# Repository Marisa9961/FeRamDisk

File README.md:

# FeRamDisk: 基于 STM32G431 的铁电存储 U 盘

## 项目概述
FeRamDisk 是一款基于 **STM32G431** 主控与 **MB85RS256** 存储介质的专用闪存盘。

不同于传统的 NAND Flash 存储方案，本项目利用铁电随机存取存储器（FeRAM）的物理特性，实现了极高的读写耐久性与近乎瞬时的随机访问能力。

硬件设计中使用了四片并列的 **MB85RS256** ，单片容量为 32 kB（即 256 Kbit），总计达到的存储空间为 128 kB。

## 功能介绍

1. **硬件设计开源**：提供完整的 Kicad 工程、原理图及制造文件，可直接打板生产。
2. **USB 大容量存储设备固件设计**：基于 Rust embassy 异步框架，从零实现 SCSI 指令集与 BOT 协议，支持全平台免驱识别。
3. **影子存储区防止文件系统崩溃**：利用日志机制抽象存储操作，保障意外断电及插拔时的数据一致性。

## 快速上手

项目固件采用 Rust 编写。构建前请确保已安装 Rust 工具链。

```bash
cd firmware

# 编译固件（默认已启用 hardware feature）
cargo build --release

# 在主机上运行脱离硬件的单元测试（需关闭默认的硬件功能并指定主机平台）
# 另外需要根据自己的开发环境选择正确的目标平台
cargo test --no-default-features --target x86_64-pc-windows-msvc

# 如果已配置 probe-rs 等烧录工具，可直接一键编译并烧录
cargo run --release
```

## 项目构成

- `hardware/`: 硬件设计目录（包含 Kicad 源工程、BOM 表及 Gerber 生产文件）。
- `firmware/`: 核心固件目录（Rust 编写）。
  - `src/usb/`: USB 核心协议栈（MSC / BOT / SCSI）的具体实现。
  - `src/storage/`: 存储后端适配与事务日志系统（Journaling），确保块设备的高可靠读写。
  - `src/drivers/`: SPI 通信底漆及 MB85RS256 铁电存储芯片的驱动层。
  - `tests/`: 包含脱离硬件直接在 PC 端运行的协议栈软仿真测试环境。
- `docs/`: 相关的项目说明与文档资源。

## 贡献要点

欢迎任何形式的讨论与代码贡献（Pull Request / Issue）：
1. **固件开发**：PR 提交前，请确保能够通过 `tests/` 目录下的所有软仿真单元测试 (`cargo test`)。
2. **硬件优化**：如有 PCB 布局或元器件替代方案，请提供原因及 Kicad 源文件的修改。
3. **想法拓展**：欢迎探讨铁电特性（极快且无磨损限制）在微型数据记录器（Data Logger）等前沿领域的新用法。

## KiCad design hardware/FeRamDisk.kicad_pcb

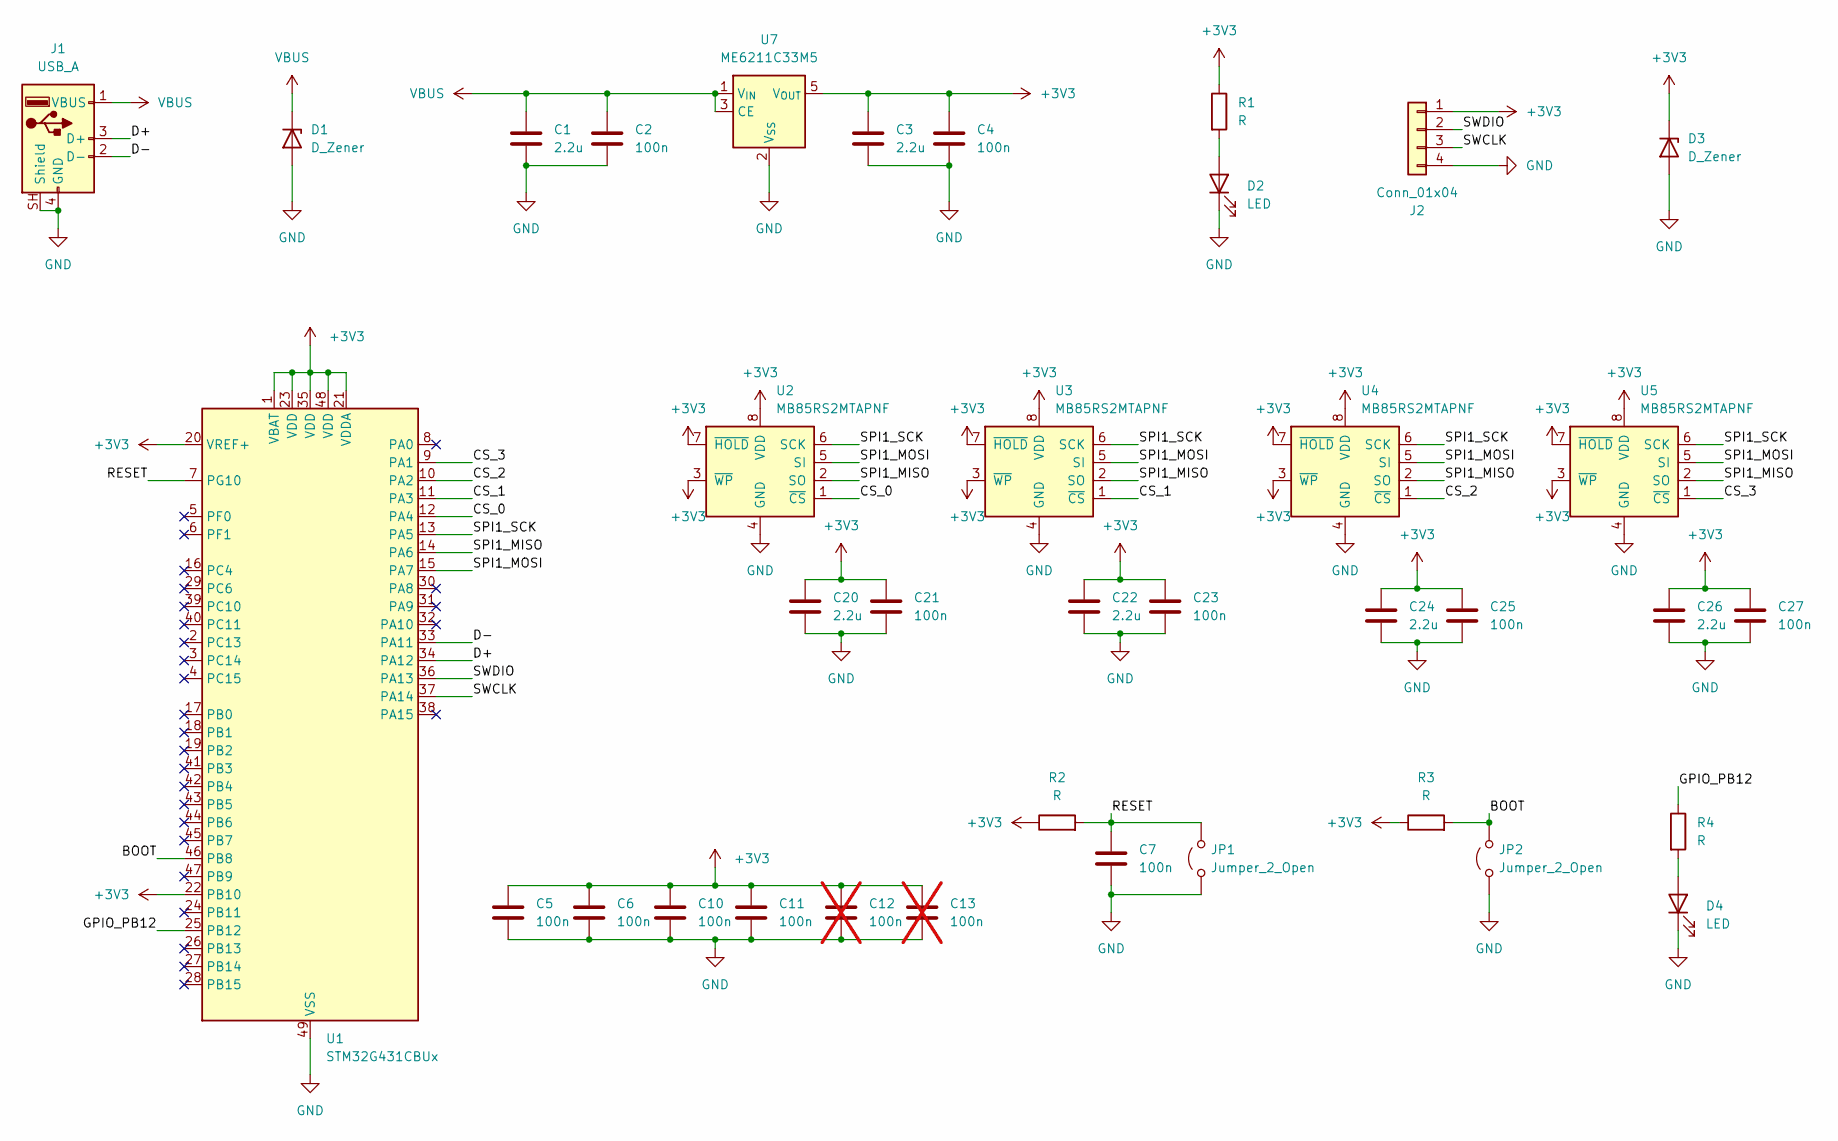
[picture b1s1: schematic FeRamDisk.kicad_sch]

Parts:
C1, C3, C20, C22, C24, C26: 2.2u; C_0603_1608Metric
C2, C4, C5, C6, C7, C10, C11, C21, C23, C25, C27: 100n; C_0603_1608Metric
C12, C13: 100n; C_0603_1608Metric; not fitted
D1, D3: D_Zener; D_SOD-123
D2, D4: LED; LED_0603_1608Metric
J1: USB_A; USB_A_CNCTech_1001-011-01101_Horizontal
J2: Conn_01x04; PinHeader_1x04_P2.54mm_Vertical
JP1, JP2: Jumper_2_Open; SolderJumper-2_P1.3mm_Open_RoundedPad1.0x1.5mm
R1, R2, R3, R4: R; R_0603_1608Metric
U1: STM32G431CBUx; QFN-48-1EP_7x7mm_P0.5mm_EP5.6x5.6mm
U2, U3, U4, U5: MB85RS2MTAPNF; SOP-8_3.76x4.96mm_P1.27mm
U7: ME6211C33M5; SOT-23-5

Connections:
+3V3: C3.1, C4.1, C5.1, C6.1, C10.1, C11.1, C12.1, C13.1, C20.1, C21.1, C22.1, C23.1, C24.1, C25.1, C26.1, C27.1, D3.1 (K), J2.1, R1.1, R2.1, R3.1, U1.1 (VBAT), U1.20 (VREF+), U1.21 (VDDA), U1.22 (PB10), U1.23 (VDD), U1.35 (VDD), U1.48 (VDD), U2.3 (~WP), U2.7 (~HOLD), U2.8 (VDD), U3.3 (~WP), U3.7 (~HOLD), U3.8 (VDD), U4.3 (~WP), U4.7 (~HOLD), U4.8 (VDD), U5.3 (~WP), U5.7 (~HOLD), U5.8 (VDD), U7.5 (V_{OUT})
/BOOT: JP2.2 (B), R3.2, U1.46 (PB8)
/CS_0: U1.12 (PA4), U2.1 (~CS)
/CS_1: U1.11 (PA3), U3.1 (~CS)
/CS_2: U1.10 (PA2), U4.1 (~CS)
/CS_3: U1.9 (PA1), U5.1 (~CS)
/D+: J1.3 (D+), U1.34 (PA12)
/D-: J1.2 (D-), U1.33 (PA11)
/GPIO_PB12: R4.1, U1.25 (PB12)
/RESET: C7.1, JP1.2 (B), R2.2, U1.7 (PG10)
/SPI1_MISO: U1.14 (PA6), U2.2 (SO), U3.2 (SO), U4.2 (SO), U5.2 (SO)
/SPI1_MOSI: U1.15 (PA7), U2.5 (SI), U3.5 (SI), U4.5 (SI), U5.5 (SI)
/SPI1_SCK: U1.13 (PA5), U2.6 (SCK), U3.6 (SCK), U4.6 (SCK), U5.6 (SCK)
/SWCLK: J2.3, U1.37 (PA14)
/SWDIO: J2.2, U1.36 (PA13)
GND: C1.2, C2.2, C3.2, C4.2, C5.2, C6.2, C7.2, C10.2, C11.2, C12.2, C13.2, C20.2, C21.2, C22.2, C23.2, C24.2, C25.2, C26.2, C27.2, D1.2 (A), D2.1 (K), D3.2 (A), D4.1 (K), J1.4 (GND), J1.SH (Shield), J2.4, JP1.1 (A), JP2.1 (A), U1.49 (VSS), U2.4 (GND), U3.4 (GND), U4.4 (GND), U5.4 (GND), U7.2 (V_{SS})
unnamed: D2.2 (A), R1.2
unnamed: D4.2 (A), R4.2
VBUS: C1.1, C2.1, D1.1 (K), J1.1 (VBUS), U7.1 (V_{IN}), U7.3 (CE)

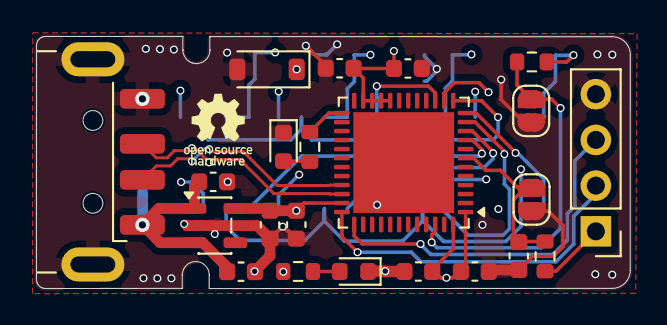
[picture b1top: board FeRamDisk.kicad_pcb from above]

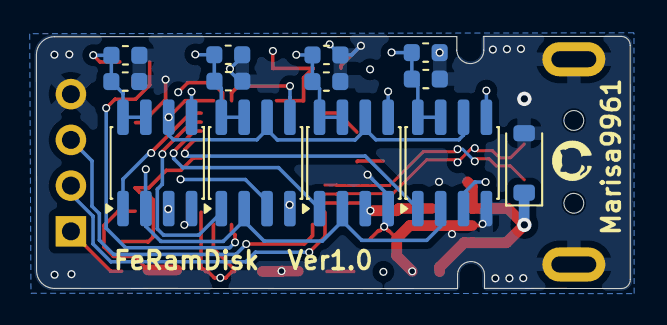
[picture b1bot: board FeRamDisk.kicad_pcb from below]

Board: 4 copper layers, 33.0 x 14.0 mm, 35 parts (13 on the bottom side), 19 nets.

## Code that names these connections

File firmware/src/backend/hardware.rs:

use crate::drivers::feram::{self, FeRam};
use crate::drivers::spi::FramSpi;
use crate::init;
use crate::storage::{
    visible_block_count_from_physical,
    MetadataJournalStorage,
    JOURNAL_RESERVED_BLOCKS,
};
use embassy_stm32::gpio::{Level, Output, Speed};
use embassy_stm32::mode::Async;
use embassy_stm32::peripherals;
use embassy_stm32::spi::{self, mode::Master, Spi};
use embassy_stm32::time::Hertz;
use embassy_stm32::usb as stm32_usb;
use embassy_stm32::{Peri, Peripherals};
use rtt_target::rprintln;

pub type HardwareStorage = MetadataJournalStorage<
    FeRam<FramSpi<'static, Output<'static>, Output<'static>, Output<'static>, Output<'static>>>,
>;

#[derive(Debug, Copy, Clone, Eq, PartialEq)]
pub enum HardwareInitError {
    MissingResource(&'static str),
    VolumeInitFailed,
    JournalInitFailed,
}

pub struct HardwareParts {
    spi: Option<Spi<'static, Async, Master>>,
    cs0: Option<Output<'static>>,
    cs1: Option<Output<'static>>,
    cs2: Option<Output<'static>>,
    cs3: Option<Output<'static>>,
    usb: Option<Peri<'static, peripherals::USB>>,
    usb_dp: Option<Peri<'static, peripherals::PA12>>,
    usb_dm: Option<Peri<'static, peripherals::PA11>>,
}

fn spi_config() -> spi::Config {
    let mut config = spi::Config::default();
    config.frequency = Hertz(4_000_000);
    config
}

fn log_capacity(physical_blocks: u32, visible_blocks: u32) {
    rprintln!(
        "FeRAM capacity: physical={} blocks, visible={} blocks",
        physical_blocks,
        visible_blocks
    );
}

pub fn init_hardware_parts(p: Peripherals) -> HardwareParts {
    let spi = Spi::new(
        p.SPI1,
        p.PA5,
        p.PA7,
        p.PA6,
        p.DMA1_CH1,
        p.DMA1_CH2,
        init::Irqs,
        spi_config(),
    );

    let cs0 = Output::new(p.PA4, Level::High, Speed::VeryHigh);
    let cs1 = Output::new(p.PA3, Level::High, Speed::VeryHigh);
    let cs2 = Output::new(p.PA2, Level::High, Speed::VeryHigh);
    let cs3 = Output::new(p.PA1, Level::High, Speed::VeryHigh);

    HardwareParts {
        spi: Some(spi),
        cs0: Some(cs0),
        cs1: Some(cs1),
        cs2: Some(cs2),
        cs3: Some(cs3),
        usb: Some(p.USB),
        usb_dp: Some(p.PA12),
        usb_dm: Some(p.PA11),
    }
}

pub async fn init_storage(parts: &mut HardwareParts) -> Result<HardwareStorage, HardwareInitError> {
    let fram_spi = FramSpi::new(
        parts
            .spi
            .take()
            .ok_or(HardwareInitError::MissingResource("SPI already consumed"))?,
        parts
            .cs0
            .take()
            .ok_or(HardwareInitError::MissingResource("CS0 already consumed"))?,
        parts
            .cs1
            .take()
            .ok_or(HardwareInitError::MissingResource("CS1 already consumed"))?,
        parts
            .cs2
            .take()
            .ok_or(HardwareInitError::MissingResource("CS2 already consumed"))?,
        parts
            .cs3
            .take()
            .ok_or(HardwareInitError::MissingResource("CS3 already consumed"))?,
    );

    let mut fram = FeRam::new(fram_spi);
    let physical_blocks = fram.block_count();
    let visible_blocks = visible_block_count_from_physical(physical_blocks);

    log_capacity(physical_blocks, visible_blocks);

    for chip_idx in 0..feram::CHIP_COUNT {
        match fram.read_id(chip_idx).await {
            Ok(id) => {
                rprintln!(
                    "Chip {}: Device ID = 0x{:02X}{:02X}{:02X}",
                    chip_idx,
                    id[0],
                    id[1],
                    id[2]
                );
            }
            Err(e) => {
                rprintln!("Chip {}: ID read failed - {:?}", chip_idx, e);
            }
        }
    }

    match fram
        .ensure_mass_storage_volume_for_total_blocks_at_offset(visible_blocks, JOURNAL_RESERVED_BLOCKS)
        .await
    {
        Ok(true) => rprintln!("Initialized FAT12 volume for Windows"),
        Ok(false) => rprintln!("FAT12 volume already present"),
        Err(e) => {
            rprintln!("Volume initialization failed: {:?}", e);
            return Err(HardwareInitError::VolumeInitFailed);
        }
    }

    let mut storage = MetadataJournalStorage::new(fram);
    if let Err(e) = storage.initialize().await {
        rprintln!("Metadata journal initialization failed: {:?}", e);
        return Err(HardwareInitError::JournalInitFailed);
    }

    Ok(storage)
}

pub fn init_usb_driver(parts: &mut HardwareParts) -> Result<stm32_usb::Driver<'static, peripherals::USB>, HardwareInitError> {
    Ok(stm32_usb::Driver::new(
        parts
            .usb
            .take()
            .ok_or(HardwareInitError::MissingResource("USB peripheral already consumed"))?,
        init::Irqs,
        parts
            .usb_dp
            .take()
            .ok_or(HardwareInitError::MissingResource("USB DP already consumed"))?,
        parts
            .usb_dm
            .take()
            .ok_or(HardwareInitError::MissingResource("USB DM already consumed"))?,
    ))
}

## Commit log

2026-03-28 feat: hardware version 1.0
2026-03-28 feat: initialize framework
2026-04-02 feat: add rtt and gpio test
2026-04-02 feat: add embassy framework
2026-04-08 feat: initial setup feram disk
2026-04-15 fix: slow spi rate; add chip id check
2026-04-16 chore: temporary 2-chip hardware configuration
2026-04-16 feat: improve msc.rs and device.rs for stability
2026-04-16 refactor: decompose usb module
2026-04-17 feat: implement journal protection
2026-04-20 refactor: decompose storage module
2026-04-23 feat: add black-box tests; refactor core implementation
2026-04-28 fix: improve protocol stack compliance and error resilience; expand test coverage
2026-05-07 test: add more usb test coverage
2026-05-08 docs: update readme
2026-05-08 chore: add github action
2026-05-08 fix: add write permissions for release action
2026-05-08 fix: enable github action draft release; update readme
